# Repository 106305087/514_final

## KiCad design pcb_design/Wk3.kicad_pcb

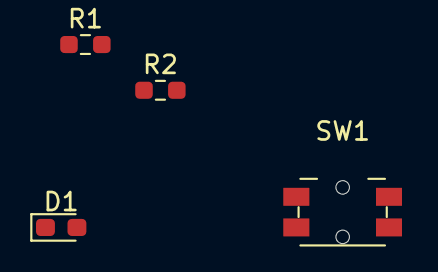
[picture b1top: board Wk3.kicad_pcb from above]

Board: 2 copper layers, 4 parts (0 on the bottom side), 3 nets, no tracks yet.

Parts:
D1: LED; LED_0603_1608Metric_Pad1.05x0.95mm_HandSolder
R1, R2: R; R_0603_1608Metric_Pad0.98x0.95mm_HandSolder
SW1: SW_SPST; Panasonic_EVQPUM_EVQPUD

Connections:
GND: D1.1 (K), R2.2
unnamed: D1.2 (A), R1.1
unnamed: R2.1, SW1.1 (A)

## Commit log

2024-01-17 update slide
2024-01-17 update again
2024-01-18 pcb design
2024-02-21 initial
